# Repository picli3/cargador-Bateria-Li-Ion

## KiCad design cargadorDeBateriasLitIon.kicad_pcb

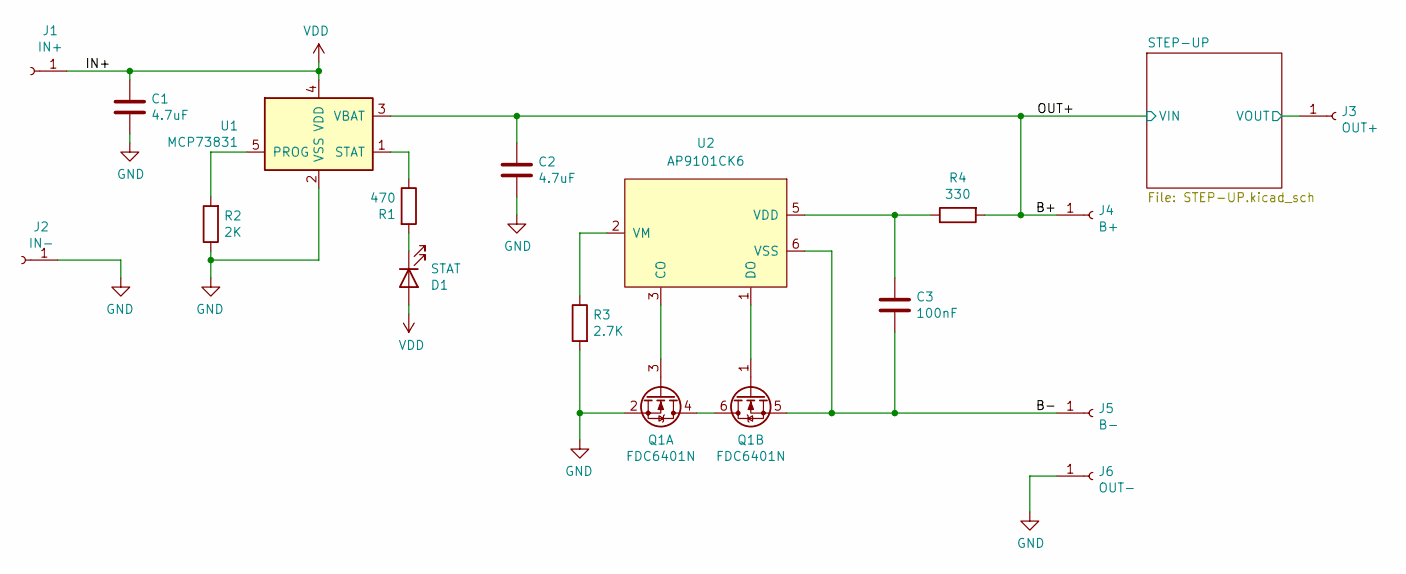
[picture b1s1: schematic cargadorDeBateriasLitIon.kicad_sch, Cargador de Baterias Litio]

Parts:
C1, C2: 4.7uF; C_0603_1608Metric; Mfg Part # CC0603ZRY5V5BB475
C3: 100nF; C_0603_1608Metric; Mfg Part # C0603C104M4RACTU
D1: STAT; LED_0603_1608Metric; Mfg Part # SML-D12U1WT86
J1: IN+; TestPoint_THTPad_1.5x1.5mm_Drill0.7mm; Mfg Part # DNP
J2: IN-; TestPoint_THTPad_1.5x1.5mm_Drill0.7mm; Mfg Part # DNP
J3: OUT+; TestPoint_THTPad_1.5x1.5mm_Drill0.7mm; Mfg Part # DNP
J4: B+; TestPoint_THTPad_1.5x1.5mm_Drill0.7mm; Mfg Part # DNP
J5: B-; TestPoint_THTPad_1.5x1.5mm_Drill0.7mm; Mfg Part # DNP
J6: OUT-; TestPoint_THTPad_1.5x1.5mm_Drill0.7mm; Mfg Part # DNP
Q1: FDC6401N; SuperSOT-6; Mfg Part # FDC6401N
R1: 470; R_0603_1608Metric; Mfg Part # RC0603JR-07470RL
R2: 2K; R_0603_1608Metric; Mfg Part # RMCF0603JT2K00
R3: 2.7K; R_0603_1608Metric; Mfg Part # RMCF0603JT2K70
R4: 330; R_0603_1608Metric; Mfg Part # CR0603-JW-331ELF
U1: MCP73831; SOT-23-5; Mfg Part # MCP73831T-2ACI/OT
U2: AP9101CK6; SOT26; Mfg Part # AP9101CK6-ADTRG1

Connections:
/B+: C2.1, J4.1, R4.2, U1.3 (VBAT); also elsewhere on the board
/B-: C3.2, J5.1, Q1.5 (S), U2.6 (VSS)
/STEP-UP/VOUT: J3.1; also elsewhere on the board
GND: C1.2, C2.2, J2.1, J6.1, Q1.2 (S), R2.1, R3.2, U1.2 (VSS); also elsewhere on the board
unnamed: C3.1, R4.1, U2.5 (VDD)
unnamed: D1.1 (K), R1.2
unnamed: Q1.1 (G), U2.1 (DO)
unnamed: Q1.3 (G), U2.3 (CO)
unnamed: Q1.4 (D), Q1.6 (D)
unnamed: R1.1, U1.1 (STAT)
unnamed: R2.2, U1.5 (PROG)
unnamed: R3.1, U2.2 (VM)
VDD: C1.1, D1.2 (A), J1.1, U1.4 (VDD)

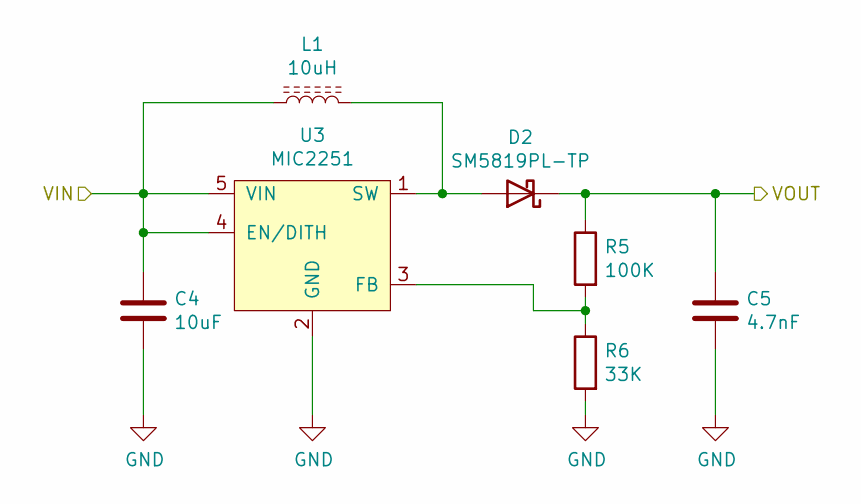
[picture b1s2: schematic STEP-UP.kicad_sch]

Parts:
C4: 10uF; C_0805_2012Metric; Mfg Part # GRM21BR61E106KA73L
C5: 4.7nF; C_0603_1608Metric; Mfg Part # CL10B472KB8NNNC
D2: SM5819PL-TP; D_SOD-123F; Mfg Part # SM5819PL-TP
L1: 10uH; L_Bourns_SDR0403; Mfg Part # SDR0403-100ML
R5: 100K; R_0603_1608Metric; Mfg Part # RC0603FR-07100KL
R6: 33K; R_0603_1608Metric; Mfg Part # RC0603FR-0733KL
U3: MIC2251; SOT-23-5; Mfg Part # MIC2251-1YD5-TR

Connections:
/B+: C4.1, L1.1, U3.4 (EN/DITH), U3.5 (VIN); also elsewhere on the board
/STEP-UP/VOUT: C5.1, D2.1 (K), R5.1; also elsewhere on the board
GND: C4.2, C5.2, R6.2, U3.2 (GND); also elsewhere on the board
unnamed: D2.2 (A), L1.2, U3.1 (SW)
unnamed: R5.2, R6.1, U3.3 (FB)

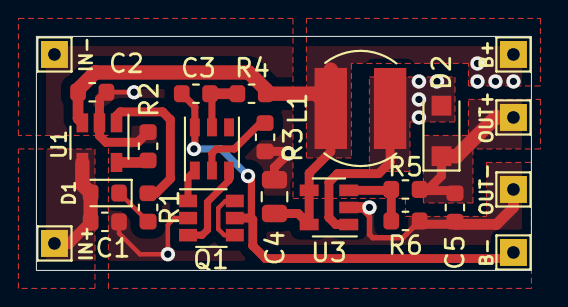
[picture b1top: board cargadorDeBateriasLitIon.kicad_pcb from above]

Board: 2 copper layers, 27.5 x 13.0 mm, 24 parts (0 on the bottom side), 15 nets.

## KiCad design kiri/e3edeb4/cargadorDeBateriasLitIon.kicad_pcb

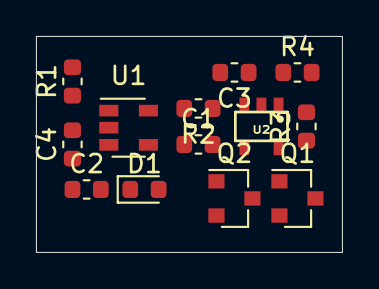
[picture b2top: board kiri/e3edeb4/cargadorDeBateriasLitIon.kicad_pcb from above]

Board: 2 copper layers, 17.0 x 12.0 mm, 13 parts (0 on the bottom side), 13 nets, no tracks yet.

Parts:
C1, C2: 4.7uF; C_0603_1608Metric
C3, C4: 100nF; C_0603_1608Metric
D1: STAT; LED_0603_1608Metric
Q1, Q2: 2N7002; SOT-23
R1: 470; R_0603_1608Metric
R2: 2K; R_0603_1608Metric
R3: 2.7K; R_0603_1608Metric
R4: 330; R_0603_1608Metric
U1: MCP73831-2; SOT-23-5
U2: AP9101C; SOT25

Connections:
/B+: C2.1, C4.1, R4.2, U1.3
/B-: C3.2, Q2.2, U2.3
/IN+: C1.1, D1.2, U1.4
GND: C1.2, C2.2, C4.2, R2.1, U1.2
unnamed: C3.1, R4.1, U2.2
unnamed: D1.1, R1.2
unnamed: Q1.1, U2.5
unnamed: Q1.2, Q2.3
unnamed: Q1.3, R3.1
unnamed: Q2.1, U2.4
unnamed: R1.1, U1.1
unnamed: R2.2, U1.5
unnamed: R3.2, U2.1

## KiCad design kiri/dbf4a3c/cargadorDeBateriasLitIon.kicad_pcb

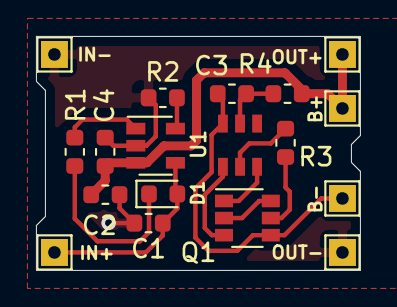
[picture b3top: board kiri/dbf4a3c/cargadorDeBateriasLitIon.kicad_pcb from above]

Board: 2 copper layers, 18.0 x 13.0 mm, 18 parts (0 on the bottom side), 13 nets.

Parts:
C1, C2: 4.7uF; C_0603_1608Metric
C3, C4: 100nF; C_0603_1608Metric
D1: STAT; LED_0603_1608Metric
J1: IN+; TestPoint_THTPad_1.5x1.5mm_Drill0.7mm
J2: IN-; TestPoint_THTPad_1.5x1.5mm_Drill0.7mm
J3: OUT+; TestPoint_THTPad_1.5x1.5mm_Drill0.7mm
J4: B+; TestPoint_THTPad_1.5x1.5mm_Drill0.7mm
J5: B-; TestPoint_THTPad_1.5x1.5mm_Drill0.7mm
J6: OUT-; TestPoint_THTPad_1.5x1.5mm_Drill0.7mm
Q1: FDC6401N; SuperSOT-6
R1: 470; R_0603_1608Metric
R2: 2K; R_0603_1608Metric
R3: 2.7K; R_0603_1608Metric
R4: 330; R_0603_1608Metric
U1: MCP73831; SOT-23-5
U2: AP9101CK6; SOT26

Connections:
/B+: C2.1, C4.1, J3.1, J4.1, R4.2, U1.3
/B-: C3.2, J5.1, Q1.4, U2.6
/IN+: C1.1, D1.2, J1.1, U1.4
GND: C1.2, C2.2, C4.2, J2.1, J6.1, R2.1, U1.2
unnamed: C3.1, R4.1, U2.5
unnamed: D1.1, R1.2
unnamed: Q1.1, U2.3
unnamed: Q1.2, Q1.6
unnamed: Q1.3, U2.1
unnamed: Q1.5, R3.1
unnamed: R1.1, U1.1
unnamed: R2.2, U1.5
unnamed: R3.2, U2.2

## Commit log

2020-08-29 falta hacer ruteo
2020-09-02 PCB version 1, falta probar
2020-09-04 generando gerber, faltan optimizar mas las pistas
2020-11-14 agregando fuente de voltaje constante a 5V
2020-11-18 resolviendo error del componente AP9101CK6
2022-06-12 pasado a kicad 6
